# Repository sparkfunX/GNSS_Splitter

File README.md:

# SparkX GNSS Antenna Splitter (Power Divider) with DC Pass

<p align="center">

</p>

*[SparkX GNSS Antenna Splitter (Power Divider) with DC Pass (SPX-21223)](https://www.sparkfun.com/products/21223)*

The [SparkX GNSS Antenna Splitter (Power Divider) with DC Pass (SPX-21223)](https://www.sparkfun.com/products/21223) lets you connect a single GNSS antenna to two boards or modules. It splits (divides) the antenna signal from Port S equally between Port 1 and Port 2. It is the perfect accessory for our [NEO-D9S correction data receiver](https://www.sparkfun.com/products/19390), allowing you to feed both the NEO-D9S and a separate GNSS module from a single antenna.

Our board is based on the BP2G1+ 2-way 50Ω DC Pass Power Splitter from Mini-Circuits. It covers the L-band frequencies from 1200 to 2000 MHz. The three ports are equipped with robust standard-polarity SMA sockets. We have an SMA Male-Male adapter available as an accessory should you want to change any or all sockets into plugs.

By default, the splitter will pass DC power from Port 1 to the antenna (Port S) so you can power your active antenna. However, it is easy to change this if required:

* By opening Jumper 1 and closing Jumper 2, you can provide DC power from Port 2 instead.
* With Jumper 1 open, you can also provide DC power from either the on-board Qwiic connector or via the VCC and GND breakout pads.
* With Jumper 1 open and both Qwiic and VCC disconnected, you can use our board as a passive 50:50 signal divider or combiner.

If your antenna needs 3.3V, Qwiic could be a good choice for you. The VCC and GND breakout pads will allow you to feed in a higher voltage (e.g. 5V) if required.

We have included a 10Ω current-limiting resistor for the Qwiic and VCC power connections, to help prevent damage if the antenna cable becomes shorted. If your antenna needs more than approx. 30mA, you can close the I<sub>lim</sub> jumper to bypass the resistor.

## Repository Contents

* **[/Documents](/Documents/)** - BP2G1+ datasheet
* **[/Hardware](/Hardware/)** - Eagle design files (.brd, .sch), Schematic, Board Dimensions

## Product Versions

* [SPX-21223](https://www.sparkfun.com/products/21223) - SparkX GNSS Antenna Splitter (Power Divider) with DC Pass - Initial SparkX Release

## License Information

This product is _**open source**_! 

Please review the LICENSE.md file for license information. 

If you have any questions or concerns on licensing, please contact technical support on our [SparkFun forums](https://forum.sparkfun.com/viewforum.php?f=152).

Distributed as-is; no warranty is given.

- Your friends at SparkFun.

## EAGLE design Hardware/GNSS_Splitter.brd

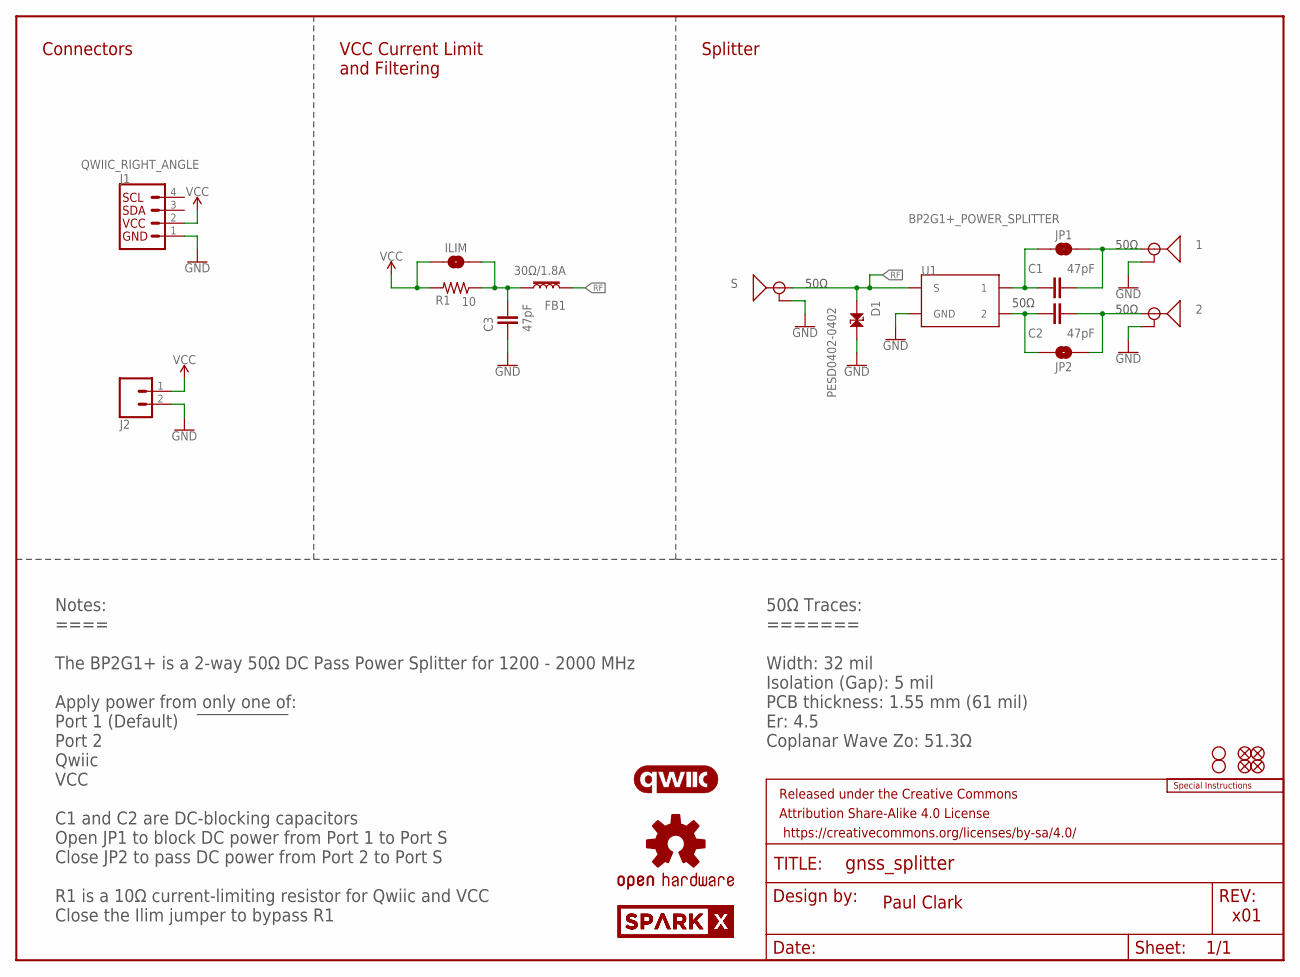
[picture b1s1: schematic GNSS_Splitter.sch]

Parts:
1, 2: ANTENNA-SMA-GROUNDEDEDGE_SMA; SMA-EDGE
C1, C2, C3: 47pF; 0603
D1: PESD0402-0402; 0402
FB1: 30Ω/1.8A; 0603
FD1, FD2, FD3, FD4: FIDUCIAL1X2; FIDUCIAL-1X2
FRAME1: FRAME-LETTER; CREATIVE_COMMONS
H1, H2: STAND-OFF
ILIM: JUMPER-SMT_2_NO_SILK; SMT-JUMPER_2_NO_SILK
J1: QWIIC_RIGHT_ANGLE; JST04_1MM_RA
J2: CONN_021X02_NO_SILK; 1X02_NO_SILK
JP1: JUMPER-SMT_2_NC_TRACE_SILK; SMT-JUMPER_2_NC_TRACE_SILK
JP2: JUMPER-SMT_2_NO_SILK; SMT-JUMPER_2_NO_SILK
LOGO1: OSHW-LOGOS; OSHW-LOGO-S
LOGO2: QWIIC_LOGO_6MM; QWIIC_6MM
LOGO3: SPECIAL_INSTRUCTIONS-ORDERING; ORDERING_INSTRUCTIONS
R1: 10; 0603
S: ANTENNA-SMA-GROUNDEDEDGE_SMA; SMA-EDGE
U1: BP2G1+_POWER_SPLITTER; XX21
U$1, U$2: SPARKX-LOGO3; SPARKX-SMALL

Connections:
GND: 1.GND@0 (GND), 1.GND@1 (GND), 1.GND@2 (GND), 1.GND@3 (GND), 2.GND@0 (GND), 2.GND@1 (GND), 2.GND@2 (GND), 2.GND@3 (GND), C3.1, D1.2, J1.1, J2.2, S.GND@0 (GND), S.GND@1 (GND), S.GND@2 (GND), S.GND@3 (GND), U1.1 (GND), U1.3 (GND), U1.4 (GND), U1.6 (GND), U1.7 (GND)
unnamed: C1.1, JP1.1, U1.8 (1)
unnamed: C3.2, FB1.1, ILIM.2, R1.1
unnamed: C2.2, JP2.2, U1.5 (2)
unnamed: 2.SIG (SIGNAL), C2.1, JP2.1
unnamed: 1.SIG (SIGNAL), C1.2, JP1.2
RF: D1.1, FB1.2, S.SIG (SIGNAL), U1.2 (S)
VCC: ILIM.1, J1.2, J2.1, R1.2

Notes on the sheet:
Paul Clark
x01
Notes: ==== The BP2G1+ is a 2-way 50Ω DC Pass Power Splitter for 1200 - 2000 MHz Apply power from only one of: Port 1 (Default) Port 2 Qwiic VCC C1 and C2 are DC-blocking capacitors Open JP1 to block DC power from Port 1 to Port S Close JP2 to pass DC power from Port 2 to Port S R1 is a 10Ω current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
50Ω
50Ω Traces: ======= Width: 32 mil Isolation (Gap): 5 mil PCB thickness: 1.55 mm (61 mil) Er: 4.5 Coplanar Wave Zo: 51.3Ω
Connectors
VCC Current Limit and Filtering
Splitter

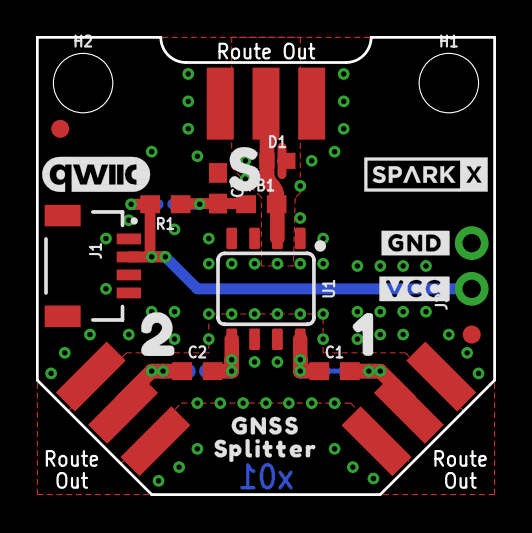
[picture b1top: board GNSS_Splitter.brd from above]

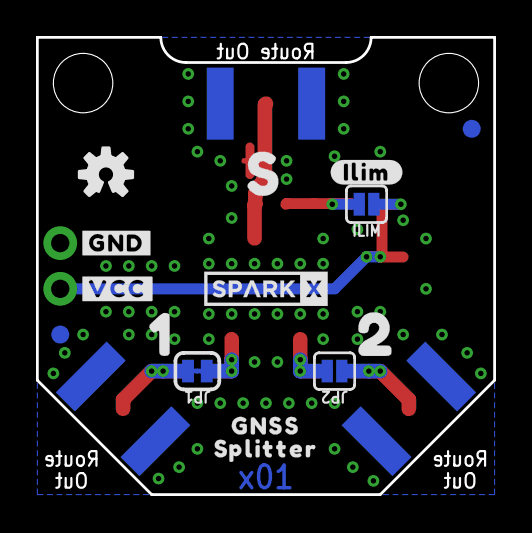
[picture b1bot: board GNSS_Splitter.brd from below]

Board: 2 copper layers, 25.4 x 25.4 mm, 44 parts (16 on the bottom side), 8 nets.

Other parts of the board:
U$3, U$7: 10
U$4, U$8: 20
U$5, U$6: S0
U$9: #GND#0
U$10: #GND#1
U$11: #VCC#0
U$12: #VCC#1
U$13, U$16: GNSS0
U$14, U$18: P0
U$15, U$17: S__LITTER0
U$19: #ILIM#0

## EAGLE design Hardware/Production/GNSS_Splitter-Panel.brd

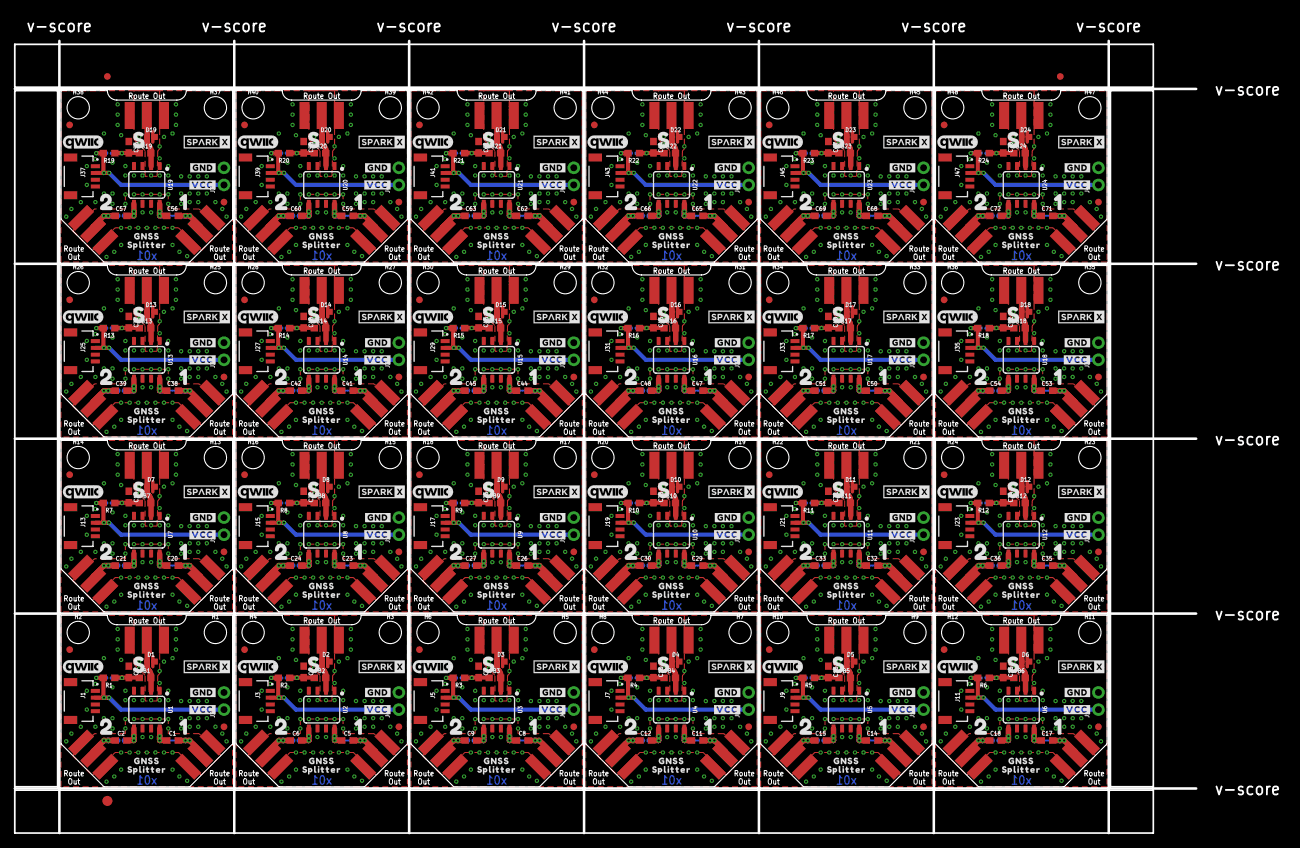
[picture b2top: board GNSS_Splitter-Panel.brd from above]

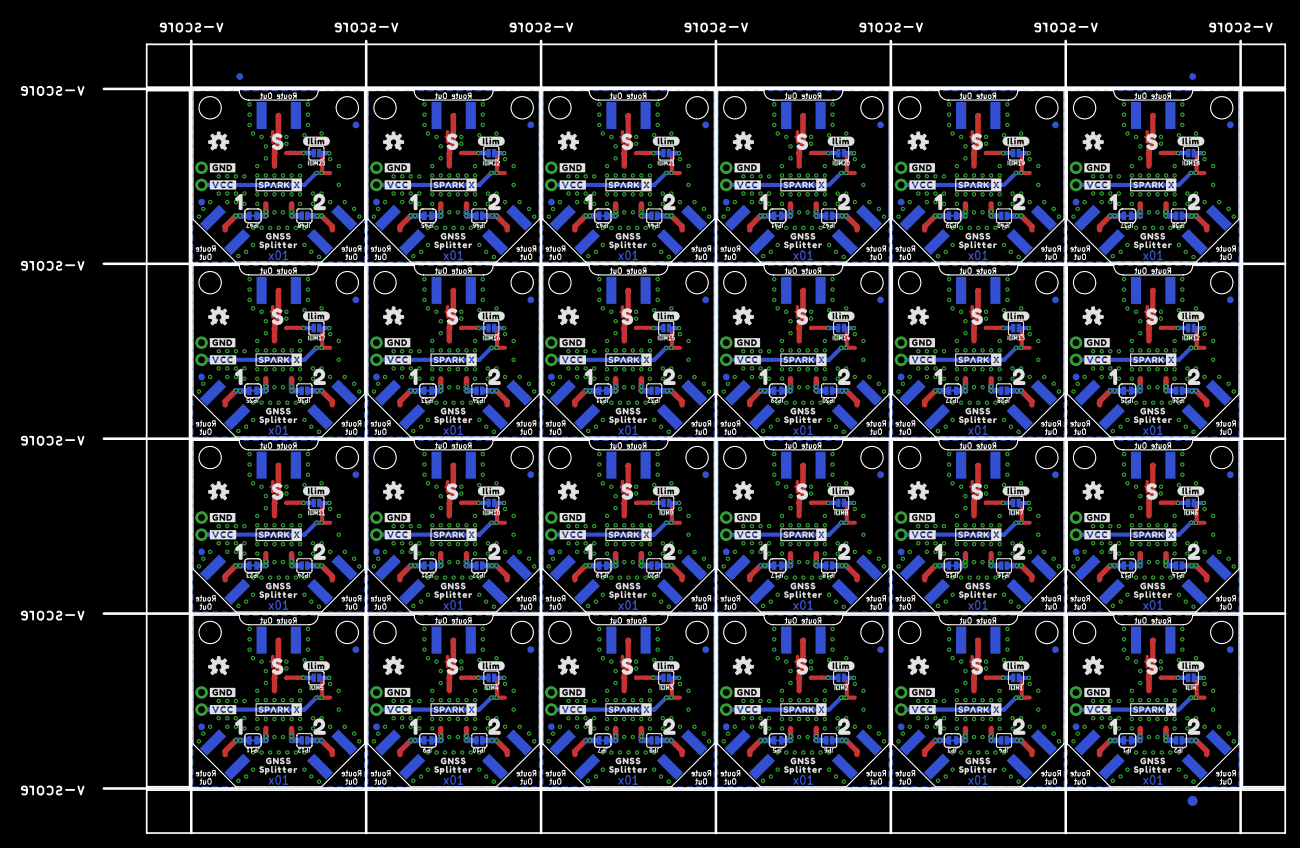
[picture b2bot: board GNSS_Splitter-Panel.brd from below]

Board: 2 copper layers, 188.2 x 121.2 mm, 1014 parts (387 on the bottom side), 192 nets.

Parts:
1, 2, 3, 4, 5, 6, 7, 8, 9, 10, 11, 12, 13, 14, 15, 16, 17, 18, 19, 20, 21, 22, 23, 24, 25, 26, 27, 28, 29, 30, 31, 32, 33, 34, 35, 36, 37, 38, 39, 40, 41, 42, 43, 44, 45, 46, 47, 48: ANTENNA-SMA-GROUNDEDEDGE_SMA; SMA-EDGE
C1, C2, C3, C4, C5, C6, C7, C8, C9, C10, C11, C12, C13, C14, C15, C16, C17, C18, C19, C20, C21, C22, C23, C24, C25, C26, C27, C28, C29, C30, C31, C32, C33, C34, C35, C36, C37, C38, C39, C40, C41, C42, C43, C44, C45, C46, C47, C48, C49, C50, C51, C52, C53, C54, C55, C56, C57, C58, C59, C60, C61, C62, C63, C64, C65, C66, C67, C68, C69, C70, C71, C72: 47pF; 0603
D1, D2, D3, D4, D5, D6, D7, D8, D9, D10, D11, D12, D13, D14, D15, D16, D17, D18, D19, D20, D21, D22, D23, D24: PESD0402-0402; 0402
E$1, E$2, E$3, E$4: FIDUCIAL-1X2
E$5, E$6: FIDUCIAL-1.5X3
FB1, FB2, FB3, FB4, FB5, FB6, FB7, FB8, FB9, FB10, FB11, FB12, FB13, FB14, FB15, FB16, FB17, FB18, FB19, FB20, FB21, FB22, FB23, FB24: 30Ω/1.8A; 0603
FD1, FD2, FD3, FD4, FD5, FD6, FD7, FD8, FD9, FD10, FD11, FD12, FD13, FD14, FD15, FD16, FD17, FD18, FD19, FD20, FD21, FD22, FD23, FD24, FD25, FD26, FD27, FD28, FD29, FD30, FD31, FD32, FD33, FD34, FD35, FD36, FD37, FD38, FD39, FD40, FD41, FD42, FD43, FD44, FD45, FD46, FD47, FD48, FD49, FD50, FD51, FD52, FD53, FD54, FD55, FD56, FD57, FD58, FD59, FD60, FD61, FD62, FD63, FD64, FD65, FD66, FD67, FD68, FD69, FD70, FD71, FD72, FD73, FD74, FD75, FD76, FD77, FD78, FD79, FD80, FD81, FD82, FD83, FD84, FD85, FD86, FD87, FD88, FD89, FD90, FD91, FD92, FD93, FD94, FD95, FD96: FIDUCIAL1X2; FIDUCIAL-1X2
H1, H2, H3, H4, H5, H6, H7, H8, H9, H10, H11, H12, H13, H14, H15, H16, H17, H18, H19, H20, H21, H22, H23, H24, H25, H26, H27, H28, H29, H30, H31, H32, H33, H34, H35, H36, H37, H38, H39, H40, H41, H42, H43, H44, H45, H46, H47, H48: STAND-OFF
ILIM, ILIM1, ILIM2, ILIM3, ILIM4, ILIM5, ILIM6, ILIM7, ILIM8, ILIM9, ILIM10, ILIM11, ILIM12, ILIM13, ILIM14, ILIM15, ILIM16, ILIM17, ILIM18, ILIM19, ILIM20, ILIM21, ILIM22, ILIM23: JUMPER-SMT_2_NO_SILK; SMT-JUMPER_2_NO_SILK
J1, J3, J5, J7, J9, J11, J13, J15, J17, J19, J21, J23, J25, J27, J29, J31, J33, J35, J37, J39, J41, J43, J45, J47: QWIIC_RIGHT_ANGLE; JST04_1MM_RA
J2, J4, J6, J8, J10, J12, J14, J16, J18, J20, J22, J24, J26, J28, J30, J32, J34, J36, J38, J40, J42, J44, J46, J48: 1X02_NO_SILK
JP1, JP3, JP5, JP7, JP9, JP11, JP13, JP15, JP17, JP19, JP21, JP23, JP25, JP27, JP29, JP31, JP33, JP35, JP37, JP39, JP41, JP43, JP45, JP47: JUMPER-SMT_2_NC_TRACE_SILK; SMT-JUMPER_2_NC_TRACE_SILK
JP2, JP4, JP6, JP8, JP10, JP12, JP14, JP16, JP18, JP20, JP22, JP24, JP26, JP28, JP30, JP32, JP34, JP36, JP38, JP40, JP42, JP44, JP46, JP48: JUMPER-SMT_2_NO_SILK; SMT-JUMPER_2_NO_SILK
LOGO1, LOGO3, LOGO5, LOGO7, LOGO9, LOGO11, LOGO13, LOGO15, LOGO17, LOGO19, LOGO21, LOGO23, LOGO25, LOGO27, LOGO29, LOGO31, LOGO33, LOGO35, LOGO37, LOGO39, LOGO41, LOGO43, LOGO45, LOGO47: OSHW-LOGOS; OSHW-LOGO-S
LOGO2, LOGO4, LOGO6, LOGO8, LOGO10, LOGO12, LOGO14, LOGO16, LOGO18, LOGO20, LOGO22, LOGO24, LOGO26, LOGO28, LOGO30, LOGO32, LOGO34, LOGO36, LOGO38, LOGO40, LOGO42, LOGO44, LOGO46, LOGO48: QWIIC_LOGO_6MM; QWIIC_6MM
R1, R2, R3, R4, R5, R6, R7, R8, R9, R10, R11, R12, R13, R14, R15, R16, R17, R18, R19, R20, R21, R22, R23, R24: 10; 0603
S, S1, S2, S3, S4, S5, S6, S7, S8, S9, S10, S11, S12, S13, S14, S15, S16, S17, S18, S19, S20, S21, S22, S23: ANTENNA-SMA-GROUNDEDEDGE_SMA; SMA-EDGE
U1, U2, U3, U4, U5, U6, U7, U8, U9, U10, U11, U12, U13, U14, U15, U16, U17, U18, U19, U20, U21, U22, U23, U24: BP2G1+_POWER_SPLITTER; XX21
U$1, U$2, U$20, U$21, U$39, U$40, U$58, U$59, U$77, U$78, U$96, U$97, U$115, U$116, U$134, U$135, U$153, U$154, U$172, U$173, U$191, U$192, U$210, U$211, U$229, U$230, U$248, U$249, U$267, U$268, U$286, U$287, U$305, U$306, U$324, U$325, U$343, U$344, U$362, U$363, U$381, U$382, U$400, U$401, U$419, U$420, U$438, U$439: SPARKX-LOGO3; SPARKX-SMALL
U$3, U$7, U$22, U$26, U$41, U$45, U$60, U$64, U$79, U$83, U$98, U$102, U$117, U$121, U$136, U$140, U$155, U$159, U$174, U$178, U$193, U$197, U$212, U$216, U$231, U$235, U$250, U$254, U$269, U$273, U$288, U$292, U$307, U$311, U$326, U$330, U$345, U$349, U$364, U$368, U$383, U$387, U$402, U$406, U$421, U$425, U$440, U$444: 10
U$4, U$8, U$23, U$27, U$42, U$46, U$61, U$65, U$80, U$84, U$99, U$103, U$118, U$122, U$137, U$141, U$156, U$160, U$175, U$179, U$194, U$198, U$213, U$217, U$232, U$236, U$251, U$255, U$270, U$274, U$289, U$293, U$308, U$312, U$327, U$331, U$346, U$350, U$365, U$369, U$384, U$388, U$403, U$407, U$422, U$426, U$441, U$445: 20
U$5, U$6, U$24, U$25, U$43, U$44, U$62, U$63, U$81, U$82, U$100, U$101, U$119, U$120, U$138, U$139, U$157, U$158, U$176, U$177, U$195, U$196, U$214, U$215, U$233, U$234, U$252, U$253, U$271, U$272, U$290, U$291, U$309, U$310, U$328, U$329, U$347, U$348, U$366, U$367, U$385, U$386, U$404, U$405, U$423, U$424, U$442, U$443: S0
U$9, U$28, U$47, U$66, U$85, U$104, U$123, U$142, U$161, U$180, U$199, U$218, U$237, U$256, U$275, U$294, U$313, U$332, U$351, U$370, U$389, U$408, U$427, U$446: #GND#0
U$10, U$29, U$48, U$67, U$86, U$105, U$124, U$143, U$162, U$181, U$200, U$219, U$238, U$257, U$276, U$295, U$314, U$333, U$352, U$371, U$390, U$409, U$428, U$447: #GND#1
U$11, U$37, U$56, U$75, U$94, U$113, U$132, U$151, U$170, U$189, U$208, U$227, U$246, U$265, U$284, U$303, U$322, U$341, U$360, U$379, U$398, U$417, U$436, U$455: #VCC#0
U$12, U$38, U$57, U$76, U$95, U$114, U$133, U$152, U$171, U$190, U$209, U$228, U$247, U$266, U$285, U$304, U$323, U$342, U$361, U$380, U$399, U$418, U$437, U$456: #VCC#1
U$13, U$16, U$30, U$33, U$49, U$52, U$68, U$71, U$87, U$90, U$106, U$109, U$125, U$128, U$144, U$147, U$163, U$166, U$182, U$185, U$201, U$204, U$220, U$223, U$239, U$242, U$258, U$261, U$277, U$280, U$296, U$299, U$315, U$318, U$334, U$337, U$353, U$356, U$372, U$375, U$391, U$394, U$410, U$413, U$429, U$432, U$448, U$451: GNSS0
U$14, U$18, U$32, U$35, U$51, U$54, U$70, U$73, U$89, U$92, U$108, U$111, U$127, U$130, U$146, U$149, U$165, U$168, U$184, U$187, U$203, U$206, U$222, U$225, U$241, U$244, U$260, U$263, U$279, U$282, U$298, U$301, U$317, U$320, U$336, U$339, U$355, U$358, U$374, U$377, U$393, U$396, U$412, U$415, U$431, U$434, U$450, U$453: P0
U$15, U$17, U$31, U$34, U$50, U$53, U$69, U$72, U$88, U$91, U$107, U$110, U$126, U$129, U$145, U$148, U$164, U$167, U$183, U$186, U$202, U$205, U$221, U$224, U$240, U$243, U$259, U$262, U$278, U$281, U$297, U$300, U$316, U$319, U$335, U$338, U$354, U$357, U$373, U$376, U$392, U$395, U$411, U$414, U$430, U$433, U$449, U$452: S__LITTER0
U$19, U$36, U$55, U$74, U$93, U$112, U$131, U$150, U$169, U$188, U$207, U$226, U$245, U$264, U$283, U$302, U$321, U$340, U$359, U$378, U$397, U$416, U$435, U$454: #ILIM#0

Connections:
GND: 1.GND@0, 1.GND@1, 1.GND@2, 1.GND@3, 2.GND@0, 2.GND@1, 2.GND@2, 2.GND@3, C3.1, D1.2, J1.1, J2.2, S.GND@0, S.GND@1, S.GND@2, S.GND@3, U1.1, U1.3, U1.4, U1.6, U1.7
GND1: 3.GND@0, 3.GND@1, 3.GND@2, 3.GND@3, 4.GND@0, 4.GND@1, 4.GND@2, 4.GND@3, C4.1, D2.2, J3.1, J4.2, S1.GND@0, S1.GND@1, S1.GND@2, S1.GND@3, U2.1, U2.3, U2.4, U2.6, U2.7
GND2: 5.GND@0, 5.GND@1, 5.GND@2, 5.GND@3, 6.GND@0, 6.GND@1, 6.GND@2, 6.GND@3, C7.1, D3.2, J5.1, J6.2, S2.GND@0, S2.GND@1, S2.GND@2, S2.GND@3, U3.1, U3.3, U3.4, U3.6, U3.7
GND3: 7.GND@0, 7.GND@1, 7.GND@2, 7.GND@3, 8.GND@0, 8.GND@1, 8.GND@2, 8.GND@3, C10.1, D4.2, J7.1, J8.2, S3.GND@0, S3.GND@1, S3.GND@2, S3.GND@3, U4.1, U4.3, U4.4, U4.6, U4.7
GND4: 9.GND@0, 9.GND@1, 9.GND@2, 9.GND@3, 10.GND@0, 10.GND@1, 10.GND@2, 10.GND@3, C13.1, D5.2, J9.1, J10.2, S4.GND@0, S4.GND@1, S4.GND@2, S4.GND@3, U5.1, U5.3, U5.4, U5.6, U5.7
GND5: 11.GND@0, 11.GND@1, 11.GND@2, 11.GND@3, 12.GND@0, 12.GND@1, 12.GND@2, 12.GND@3, C16.1, D6.2, J11.1, J12.2, S5.GND@0, S5.GND@1, S5.GND@2, S5.GND@3, U6.1, U6.3, U6.4, U6.6, U6.7
GND6: 13.GND@0, 13.GND@1, 13.GND@2, 13.GND@3, 14.GND@0, 14.GND@1, 14.GND@2, 14.GND@3, C19.1, D7.2, J13.1, J14.2, S6.GND@0, S6.GND@1, S6.GND@2, S6.GND@3, U7.1, U7.3, U7.4, U7.6, U7.7
GND7: 15.GND@0, 15.GND@1, 15.GND@2, 15.GND@3, 16.GND@0, 16.GND@1, 16.GND@2, 16.GND@3, C22.1, D8.2, J15.1, J16.2, S7.GND@0, S7.GND@1, S7.GND@2, S7.GND@3, U8.1, U8.3, U8.4, U8.6, U8.7
GND8: 17.GND@0, 17.GND@1, 17.GND@2, 17.GND@3, 18.GND@0, 18.GND@1, 18.GND@2, 18.GND@3, C25.1, D9.2, J17.1, J18.2, S8.GND@0, S8.GND@1, S8.GND@2, S8.GND@3, U9.1, U9.3, U9.4, U9.6, U9.7
GND9: 19.GND@0, 19.GND@1, 19.GND@2, 19.GND@3, 20.GND@0, 20.GND@1, 20.GND@2, 20.GND@3, C28.1, D10.2, J19.1, J20.2, S9.GND@0, S9.GND@1, S9.GND@2, S9.GND@3, U10.1, U10.3, U10.4, U10.6, U10.7
GND10: 21.GND@0, 21.GND@1, 21.GND@2, 21.GND@3, 22.GND@0, 22.GND@1, 22.GND@2, 22.GND@3, C31.1, D11.2, J21.1, J22.2, S10.GND@0, S10.GND@1, S10.GND@2, S10.GND@3, U11.1, U11.3, U11.4, U11.6, U11.7
GND11: 23.GND@0, 23.GND@1, 23.GND@2, 23.GND@3, 24.GND@0, 24.GND@1, 24.GND@2, 24.GND@3, C34.1, D12.2, J23.1, J24.2, S11.GND@0, S11.GND@1, S11.GND@2, S11.GND@3, U12.1, U12.3, U12.4, U12.6, U12.7
GND12: 25.GND@0, 25.GND@1, 25.GND@2, 25.GND@3, 26.GND@0, 26.GND@1, 26.GND@2, 26.GND@3, C37.1, D13.2, J25.1, J26.2, S12.GND@0, S12.GND@1, S12.GND@2, S12.GND@3, U13.1, U13.3, U13.4, U13.6, U13.7
GND13: 27.GND@0, 27.GND@1, 27.GND@2, 27.GND@3, 28.GND@0, 28.GND@1, 28.GND@2, 28.GND@3, C40.1, D14.2, J27.1, J28.2, S13.GND@0, S13.GND@1, S13.GND@2, S13.GND@3, U14.1, U14.3, U14.4, U14.6, U14.7
GND14: 29.GND@0, 29.GND@1, 29.GND@2, 29.GND@3, 30.GND@0, 30.GND@1, 30.GND@2, 30.GND@3, C43.1, D15.2, J29.1, J30.2, S14.GND@0, S14.GND@1, S14.GND@2, S14.GND@3, U15.1, U15.3, U15.4, U15.6, U15.7
GND15: 31.GND@0, 31.GND@1, 31.GND@2, 31.GND@3, 32.GND@0, 32.GND@1, 32.GND@2, 32.GND@3, C46.1, D16.2, J31.1, J32.2, S15.GND@0, S15.GND@1, S15.GND@2, S15.GND@3, U16.1, U16.3, U16.4, U16.6, U16.7
GND16: 33.GND@0, 33.GND@1, 33.GND@2, 33.GND@3, 34.GND@0, 34.GND@1, 34.GND@2, 34.GND@3, C49.1, D17.2, J33.1, J34.2, S16.GND@0, S16.GND@1, S16.GND@2, S16.GND@3, U17.1, U17.3, U17.4, U17.6, U17.7
GND17: 35.GND@0, 35.GND@1, 35.GND@2, 35.GND@3, 36.GND@0, 36.GND@1, 36.GND@2, 36.GND@3, C52.1, D18.2, J35.1, J36.2, S17.GND@0, S17.GND@1, S17.GND@2, S17.GND@3, U18.1, U18.3, U18.4, U18.6, U18.7
GND18: 37.GND@0, 37.GND@1, 37.GND@2, 37.GND@3, 38.GND@0, 38.GND@1, 38.GND@2, 38.GND@3, C55.1, D19.2, J37.1, J38.2, S18.GND@0, S18.GND@1, S18.GND@2, S18.GND@3, U19.1, U19.3, U19.4, U19.6, U19.7
GND19: 39.GND@0, 39.GND@1, 39.GND@2, 39.GND@3, 40.GND@0, 40.GND@1, 40.GND@2, 40.GND@3, C58.1, D20.2, J39.1, J40.2, S19.GND@0, S19.GND@1, S19.GND@2, S19.GND@3, U20.1, U20.3, U20.4, U20.6, U20.7
GND20: 41.GND@0, 41.GND@1, 41.GND@2, 41.GND@3, 42.GND@0, 42.GND@1, 42.GND@2, 42.GND@3, C61.1, D21.2, J41.1, J42.2, S20.GND@0, S20.GND@1, S20.GND@2, S20.GND@3, U21.1, U21.3, U21.4, U21.6, U21.7
GND21: 43.GND@0, 43.GND@1, 43.GND@2, 43.GND@3, 44.GND@0, 44.GND@1, 44.GND@2, 44.GND@3, C64.1, D22.2, J43.1, J44.2, S21.GND@0, S21.GND@1, S21.GND@2, S21.GND@3, U22.1, U22.3, U22.4, U22.6, U22.7
GND22: 45.GND@0, 45.GND@1, 45.GND@2, 45.GND@3, 46.GND@0, 46.GND@1, 46.GND@2, 46.GND@3, C67.1, D23.2, J45.1, J46.2, S22.GND@0, S22.GND@1, S22.GND@2, S22.GND@3, U23.1, U23.3, U23.4, U23.6, U23.7
GND23: 47.GND@0, 47.GND@1, 47.GND@2, 47.GND@3, 48.GND@0, 48.GND@1, 48.GND@2, 48.GND@3, C70.1, D24.2, J47.1, J48.2, S23.GND@0, S23.GND@1, S23.GND@2, S23.GND@3, U24.1, U24.3, U24.4, U24.6, U24.7
unnamed: C1.1, JP1.1, U1.8
unnamed: C3.2, FB1.1, ILIM.2, R1.1
unnamed: C2.2, JP2.2, U1.5
unnamed: C5.1, JP3.1, U2.8
unnamed: 2.SIG, C2.1, JP2.1
unnamed: 1.SIG, C1.2, JP1.2
unnamed: C6.2, JP4.2, U2.5
unnamed: 3.SIG, C6.1, JP4.1
unnamed: 4.SIG, C5.2, JP3.2
unnamed: C4.2, FB2.1, ILIM1.2, R2.1
unnamed: C8.1, JP5.1, U3.8
unnamed: C9.2, JP6.2, U3.5
unnamed: 5.SIG, C9.1, JP6.1
unnamed: 6.SIG, C8.2, JP5.2
unnamed: C7.2, FB3.1, ILIM2.2, R3.1
unnamed: C11.1, JP7.1, U4.8
unnamed: C12.2, JP8.2, U4.5
unnamed: 7.SIG, C12.1, JP8.1
unnamed: 8.SIG, C11.2, JP7.2
unnamed: C10.2, FB4.1, ILIM3.2, R4.1
unnamed: C14.1, JP9.1, U5.8
unnamed: C15.2, JP10.2, U5.5
unnamed: 9.SIG, C15.1, JP10.1
unnamed: 10.SIG, C14.2, JP9.2
unnamed: C13.2, FB5.1, ILIM4.2, R5.1
unnamed: C17.1, JP11.1, U6.8
unnamed: C18.2, JP12.2, U6.5
unnamed: 11.SIG, C18.1, JP12.1
unnamed: 12.SIG, C17.2, JP11.2
unnamed: C16.2, FB6.1, ILIM5.2, R6.1
unnamed: C20.1, JP13.1, U7.8
unnamed: C21.2, JP14.2, U7.5
unnamed: 13.SIG, C21.1, JP14.1
unnamed: 14.SIG, C20.2, JP13.2
unnamed: C19.2, FB7.1, ILIM6.2, R7.1
unnamed: C23.1, JP15.1, U8.8
unnamed: C24.2, JP16.2, U8.5
unnamed: 15.SIG, C24.1, JP16.1
unnamed: 16.SIG, C23.2, JP15.2
unnamed: C22.2, FB8.1, ILIM7.2, R8.1
unnamed: C26.1, JP17.1, U9.8
unnamed: C27.2, JP18.2, U9.5
unnamed: 17.SIG, C27.1, JP18.1
unnamed: 18.SIG, C26.2, JP17.2
unnamed: C25.2, FB9.1, ILIM8.2, R9.1
unnamed: C29.1, JP19.1, U10.8
unnamed: C30.2, JP20.2, U10.5
unnamed: 19.SIG, C30.1, JP20.1
unnamed: 20.SIG, C29.2, JP19.2
unnamed: C28.2, FB10.1, ILIM9.2, R10.1
unnamed: C32.1, JP21.1, U11.8
unnamed: C33.2, JP22.2, U11.5
unnamed: 21.SIG, C33.1, JP22.1
unnamed: 22.SIG, C32.2, JP21.2
unnamed: C31.2, FB11.1, ILIM10.2, R11.1
unnamed: C35.1, JP23.1, U12.8
unnamed: C36.2, JP24.2, U12.5
unnamed: 23.SIG, C36.1, JP24.1
unnamed: 24.SIG, C35.2, JP23.2
unnamed: C34.2, FB12.1, ILIM11.2, R12.1
unnamed: C38.1, JP25.1, U13.8
unnamed: C39.2, JP26.2, U13.5
unnamed: 25.SIG, C39.1, JP26.1
unnamed: 26.SIG, C38.2, JP25.2
unnamed: C37.2, FB13.1, ILIM12.2, R13.1
unnamed: C41.1, JP27.1, U14.8
unnamed: C42.2, JP28.2, U14.5
unnamed: 27.SIG, C42.1, JP28.1
unnamed: 28.SIG, C41.2, JP27.2
unnamed: C40.2, FB14.1, ILIM13.2, R14.1
unnamed: C44.1, JP29.1, U15.8
unnamed: C45.2, JP30.2, U15.5
unnamed: 29.SIG, C45.1, JP30.1
unnamed: 30.SIG, C44.2, JP29.2
unnamed: C43.2, FB15.1, ILIM14.2, R15.1
unnamed: C47.1, JP31.1, U16.8
unnamed: C48.2, JP32.2, U16.5
unnamed: 31.SIG, C48.1, JP32.1
unnamed: 32.SIG, C47.2, JP31.2
unnamed: C46.2, FB16.1, ILIM15.2, R16.1
unnamed: C50.1, JP33.1, U17.8
unnamed: C51.2, JP34.2, U17.5
unnamed: 33.SIG, C51.1, JP34.1
unnamed: 34.SIG, C50.2, JP33.2
unnamed: C49.2, FB17.1, ILIM16.2, R17.1
unnamed: C53.1, JP35.1, U18.8
unnamed: C54.2, JP36.2, U18.5
unnamed: 35.SIG, C54.1, JP36.1
unnamed: 36.SIG, C53.2, JP35.2
unnamed: C52.2, FB18.1, ILIM17.2, R18.1
unnamed: C56.1, JP37.1, U19.8
unnamed: C57.2, JP38.2, U19.5
unnamed: 37.SIG, C57.1, JP38.1
unnamed: 38.SIG, C56.2, JP37.2
unnamed: C55.2, FB19.1, ILIM18.2, R19.1
unnamed: C59.1, JP39.1, U20.8
unnamed: C60.2, JP40.2, U20.5
unnamed: 39.SIG, C60.1, JP40.1
unnamed: 40.SIG, C59.2, JP39.2
unnamed: C58.2, FB20.1, ILIM19.2, R20.1
unnamed: C62.1, JP41.1, U21.8
unnamed: C63.2, JP42.2, U21.5
unnamed: 41.SIG, C63.1, JP42.1
unnamed: 42.SIG, C62.2, JP41.2
unnamed: C61.2, FB21.1, ILIM20.2, R21.1
unnamed: C65.1, JP43.1, U22.8
unnamed: C66.2, JP44.2, U22.5
unnamed: 43.SIG, C66.1, JP44.1
unnamed: 44.SIG, C65.2, JP43.2
unnamed: C64.2, FB22.1, ILIM21.2, R22.1
unnamed: C68.1, JP45.1, U23.8
unnamed: C69.2, JP46.2, U23.5
unnamed: 45.SIG, C69.1, JP46.1
unnamed: 46.SIG, C68.2, JP45.2
unnamed: C67.2, FB23.1, ILIM22.2, R23.1
unnamed: C71.1, JP47.1, U24.8
unnamed: C72.2, JP48.2, U24.5
unnamed: 47.SIG, C72.1, JP48.1
unnamed: 48.SIG, C71.2, JP47.2
unnamed: C70.2, FB24.1, ILIM23.2, R24.1
RF: D1.1, FB1.2, S.SIG, U1.2
RF1: D2.1, FB2.2, S1.SIG, U2.2
RF2: D3.1, FB3.2, S2.SIG, U3.2
RF3: D4.1, FB4.2, S3.SIG, U4.2
RF4: D5.1, FB5.2, S4.SIG, U5.2
RF5: D6.1, FB6.2, S5.SIG, U6.2
RF6: D7.1, FB7.2, S6.SIG, U7.2
RF7: D8.1, FB8.2, S7.SIG, U8.2
RF8: D9.1, FB9.2, S8.SIG, U9.2
RF9: D10.1, FB10.2, S9.SIG, U10.2
RF10: D11.1, FB11.2, S10.SIG, U11.2
RF11: D12.1, FB12.2, S11.SIG, U12.2
RF12: D13.1, FB13.2, S12.SIG, U13.2
RF13: D14.1, FB14.2, S13.SIG, U14.2
RF14: D15.1, FB15.2, S14.SIG, U15.2
RF15: D16.1, FB16.2, S15.SIG, U16.2
RF16: D17.1, FB17.2, S16.SIG, U17.2
RF17: D18.1, FB18.2, S17.SIG, U18.2
RF18: D19.1, FB19.2, S18.SIG, U19.2
RF19: D20.1, FB20.2, S19.SIG, U20.2
RF20: D21.1, FB21.2, S20.SIG, U21.2
RF21: D22.1, FB22.2, S21.SIG, U22.2
RF22: D23.1, FB23.2, S22.SIG, U23.2
RF23: D24.1, FB24.2, S23.SIG, U24.2
VCC: ILIM.1, J1.2, J2.1, R1.2
VCC1: ILIM1.1, J3.2, J4.1, R2.2
VCC2: ILIM2.1, J5.2, J6.1, R3.2
VCC3: ILIM3.1, J7.2, J8.1, R4.2
VCC4: ILIM4.1, J9.2, J10.1, R5.2
VCC5: ILIM5.1, J11.2, J12.1, R6.2
VCC6: ILIM6.1, J13.2, J14.1, R7.2
VCC7: ILIM7.1, J15.2, J16.1, R8.2
VCC8: ILIM8.1, J17.2, J18.1, R9.2
VCC9: ILIM9.1, J19.2, J20.1, R10.2
VCC10: ILIM10.1, J21.2, J22.1, R11.2
VCC11: ILIM11.1, J23.2, J24.1, R12.2
VCC12: ILIM12.1, J25.2, J26.1, R13.2
VCC13: ILIM13.1, J27.2, J28.1, R14.2
VCC14: ILIM14.1, J29.2, J30.1, R15.2
VCC15: ILIM15.1, J31.2, J32.1, R16.2
VCC16: ILIM16.1, J33.2, J34.1, R17.2
VCC17: ILIM17.1, J35.2, J36.1, R18.2
VCC18: ILIM18.1, J37.2, J38.1, R19.2
VCC19: ILIM19.1, J39.2, J40.1, R20.2
VCC20: ILIM20.1, J41.2, J42.1, R21.2
VCC21: ILIM21.1, J43.2, J44.1, R22.2
VCC22: ILIM22.1, J45.2, J46.1, R23.2
VCC23: ILIM23.1, J47.2, J48.1, R24.2

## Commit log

2022-09-26 Ready for review
2022-09-27 x01 PCB
2022-10-12 Add README
2023-03-28 Correct product image link

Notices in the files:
README.md:
License: CC BY-SA 4.0
parts and their libraries:
SparkFun-Aesthetics: Licensing: Creative Commons ShareAlike 4.0 International - https://creativecommons.org/licenses/by-sa/4.0
SparkFun-Aesthetics: Released under the Creative Commons Attribution Share-Alike 4.0 License
SparkFun-Aesthetics: https://creativecommons.org/licenses/by-sa/4.0
